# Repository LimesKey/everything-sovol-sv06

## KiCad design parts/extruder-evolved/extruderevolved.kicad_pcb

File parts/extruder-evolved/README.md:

A remake of the Sovol SV06 PCB with extra connectors

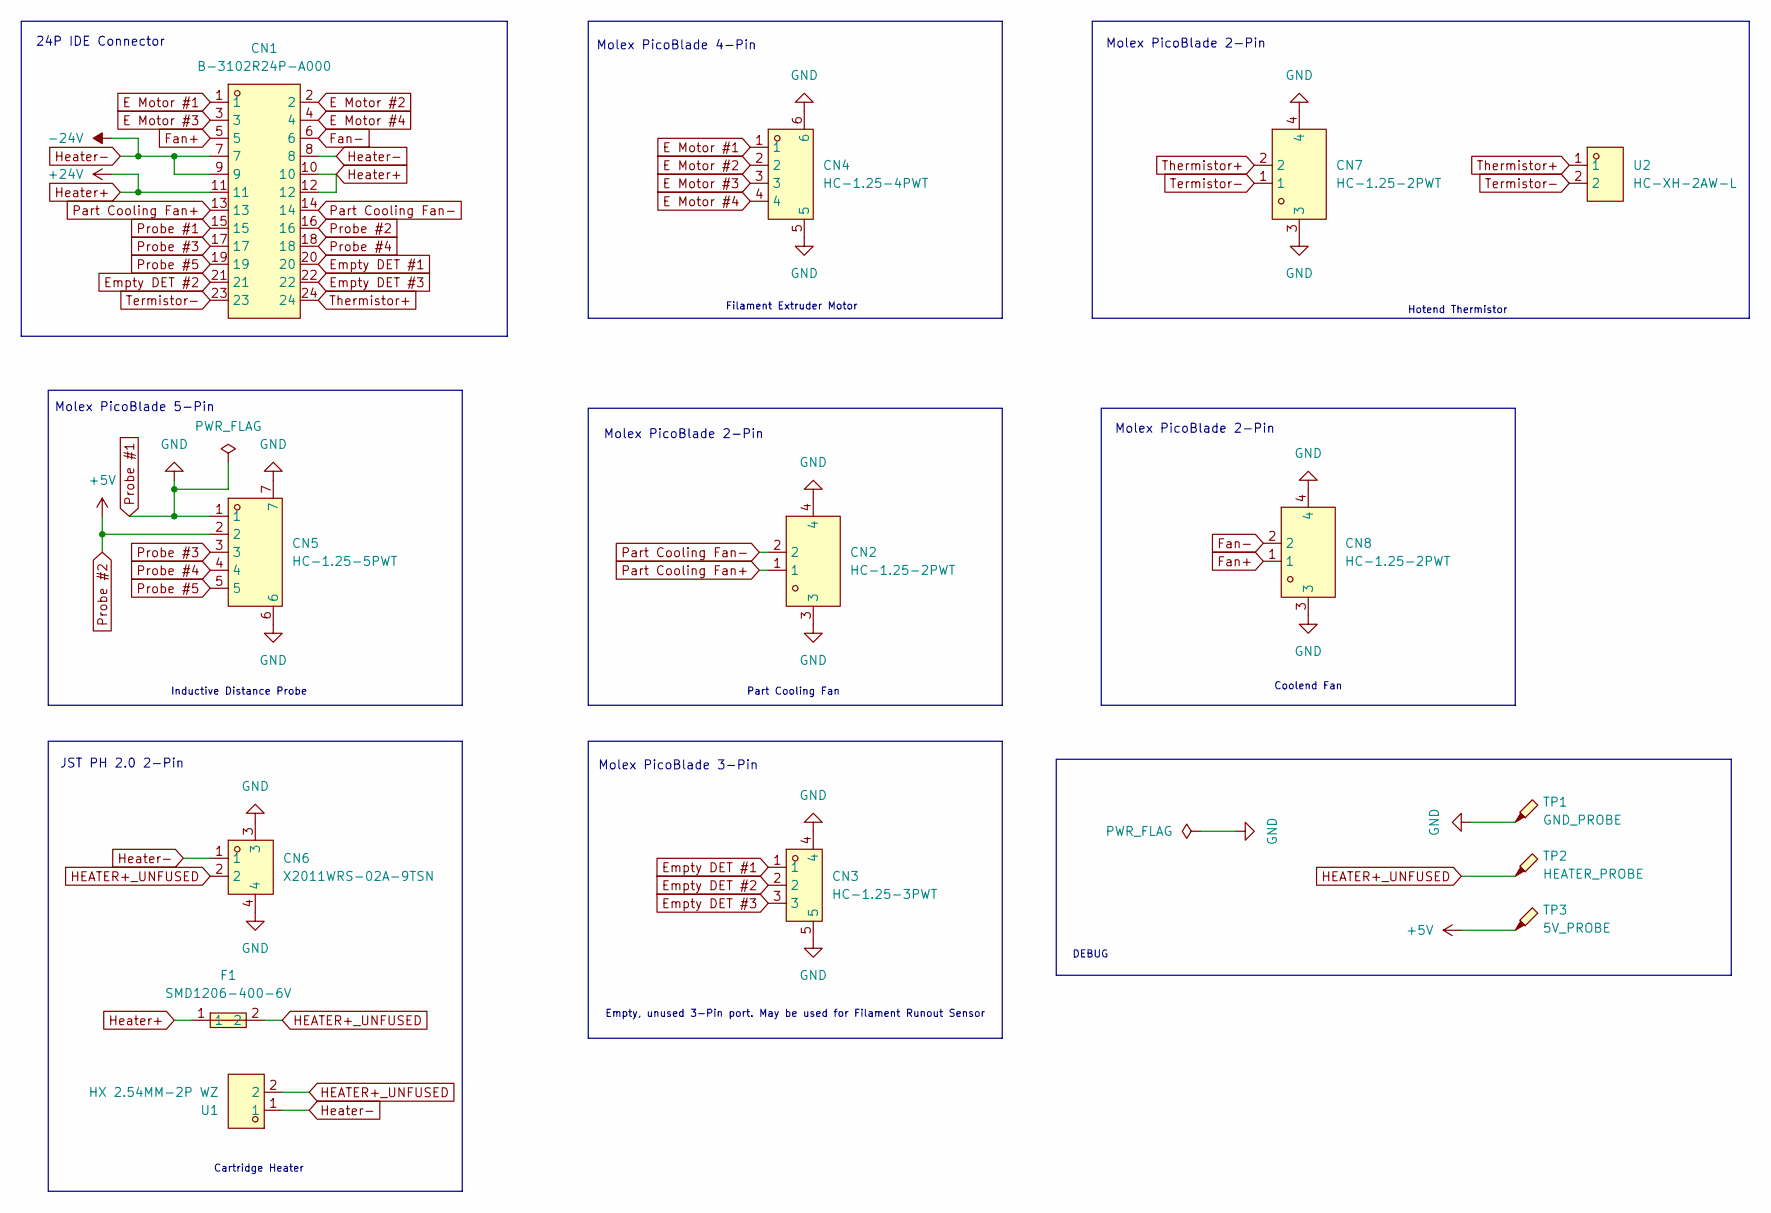
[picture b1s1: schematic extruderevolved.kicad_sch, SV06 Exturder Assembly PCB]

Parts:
CN1: B-3102R24P-A000; IDC-TH_24P-P2.00_B-3102R24P-A000; LCSC Part C383593
CN2, CN7, CN8: HC-1.25-2PWT; CONN-SMD_2P-P1.25-HC-1.25-2PWT; LCSC Part C2845379
CN3: HC-1.25-3PWT; CONN-SMD_HC-1.25-3PWT; LCSC Part C2845380
CN4: HC-1.25-4PWT; CONN-SMD_4P-P1.25-HC-1.25-4PWT; LCSC Part C2845381
CN5: HC-1.25-5PWT; CONN-SMD_5P-P1.25_HCTL_HC-1.25-5PWT; LCSC Part C2845382
CN6: X2011WRS-02A-9TSN; CONN-SMD_2P-P2.00_XKB_X2011WRS-02A-9TSN; LCSC Part C571320
F1: SMD1206-400-6V; F1206; LCSC Part C2760306
TP1: GND_PROBE; TestPoint_THTPad_D2.5mm_Drill1.2mm
TP2: HEATER_PROBE; TestPoint_THTPad_D2.5mm_Drill1.2mm
TP3: 5V_PROBE; TestPoint_THTPad_D2.5mm_Drill1.2mm
U1: HX 2.54MM-2P WZ; CONN-TH_2P-P2.50_HX-2.54MM-2P-WZ; LCSC Part C7543444
U2: HC-XH-2AW-L; CONN-TH_2P-P2.50_HC-XH-2AW-G; LCSC Part C7466689

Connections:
E Motor #1: CN1.1, CN4.1
E Motor #2: CN1.2, CN4.2
E Motor #3: CN1.3, CN4.3
E Motor #4: CN1.4, CN4.4
Empty DET #1: CN1.20, CN3.1
Empty DET #2: CN1.21, CN3.2
Empty DET #3: CN1.22, CN3.3
Fan+: CN1.5, CN8.1
Fan-: CN1.6, CN8.2
HEATER+_UNFUSED: CN6.2, F1.2, TP2.1, U1.2
Heater+: CN1.10, CN1.11, CN1.12, F1.1
Heater-: CN1.7, CN1.8, CN1.9, CN6.1, U1.1
Part Cooling Fan+: CN1.13, CN2.1
Part Cooling Fan-: CN1.14, CN2.2
Probe #1: CN1.15, CN2.3, CN2.4, CN3.4, CN3.5, CN4.5, CN4.6, CN5.1, CN5.6, CN5.7, CN6.3, CN6.4, CN7.3, CN7.4, CN8.3, CN8.4, TP1.1
Probe #2: CN1.16, CN5.2, TP3.1
Probe #3: CN1.17, CN5.3
Probe #4: CN1.18, CN5.4
Probe #5: CN1.19, CN5.5
Termistor-: CN1.23, CN7.1, U2.2
Thermistor+: CN1.24, CN7.2, U2.1

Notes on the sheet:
24P IDE Connector
Molex PicoBlade 5-Pin
Molex PicoBlade 4-Pin
Molex PicoBlade 2-Pin
JST PH 2.0 2-Pin
Inductive Distance Probe
DEBUG
Empty, unused 3-Pin port. May be used for Filament Runout Sensor
Part Cooling Fan
Filament Extruder Motor
Coolend Fan
Molex PicoBlade 3-Pin
Cartridge Heater
Hotend Thermistor

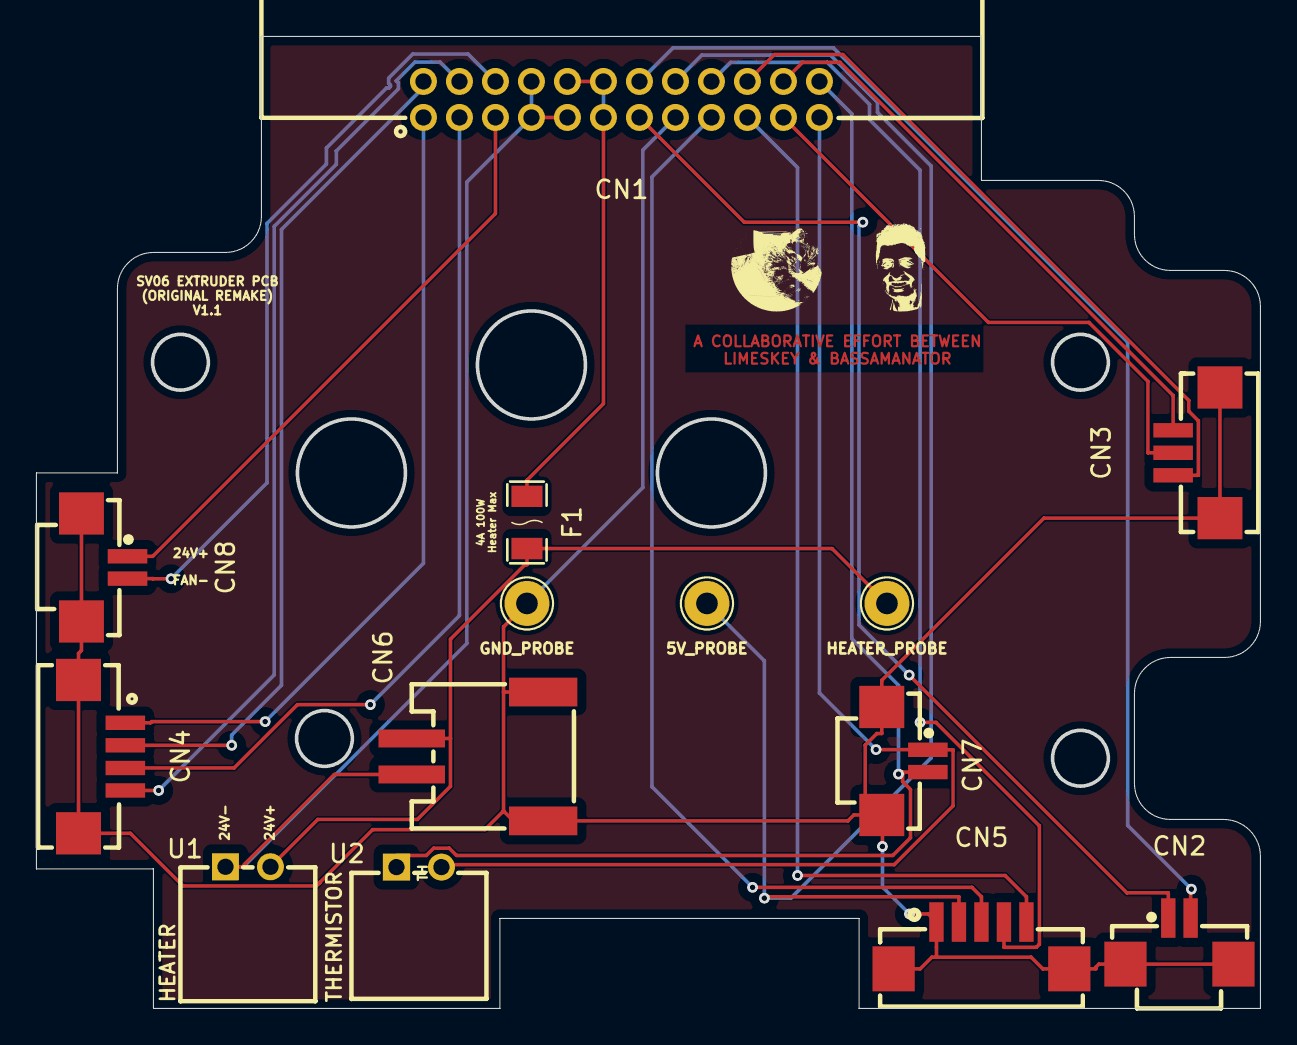
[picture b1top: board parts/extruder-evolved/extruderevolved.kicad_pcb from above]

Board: 2 copper layers, 67.9 x 53.9 mm, 15 parts (0 on the bottom side), 21 nets.

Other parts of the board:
basamator: LOGO; basa

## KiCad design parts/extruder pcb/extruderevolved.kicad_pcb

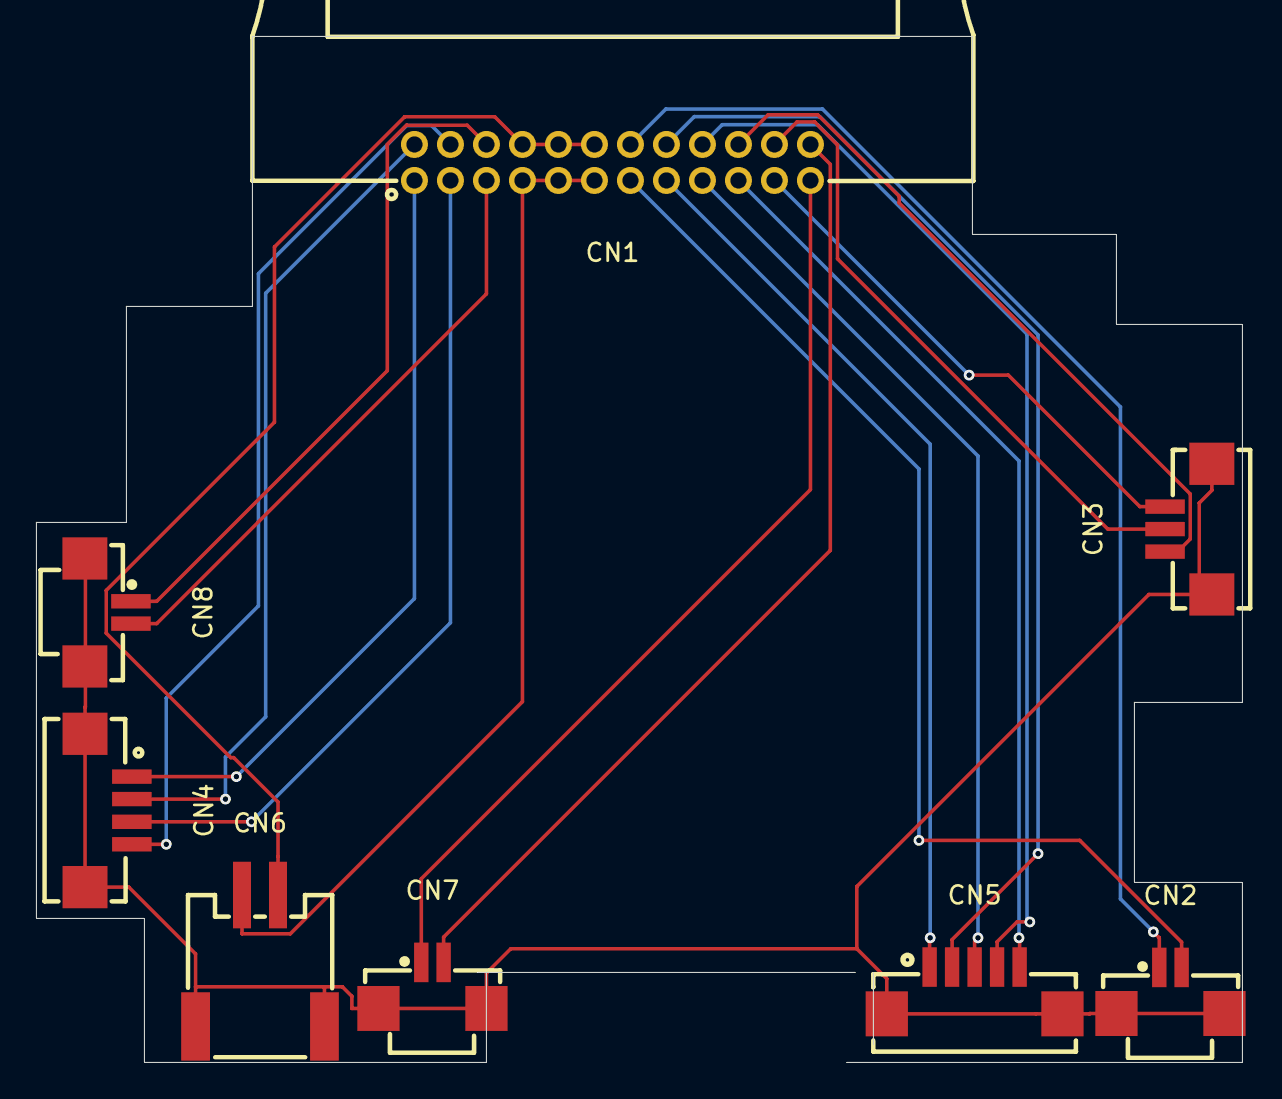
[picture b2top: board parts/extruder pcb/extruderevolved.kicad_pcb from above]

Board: 2 copper layers, 67.0 x 57.0 mm, 8 parts (0 on the bottom side), 21 nets.

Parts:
CN1: B-3102R24P-A000; IDC-TH_24P-P2.00_B-3102R24P-A000
CN2, CN7, CN8: HC-1.25-2PWT; CONN-SMD_2P-P1.25-HC-1.25-2PWT
CN3: HC-1.25-3PWT; CONN-SMD_HC-1.25-3PWT
CN4: HC-1.25-4PWT; CONN-SMD_4P-P1.25-HC-1.25-4PWT
CN5: HC-1.25-5PWT; CONN-SMD_5P-P1.25_HCTL_HC-1.25-5PWT
CN6: X2011WRS-02A-9TSN; CONN-SMD_2P-P2.00_XKB_X2011WRS-02A-9TSN

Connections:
E Motor #1: CN1.1, CN4.1
E Motor #2: CN1.2, CN4.2
E Motor #3: CN1.3, CN4.3
E Motor #4: CN1.4, CN4.4
Empty "DET" #1: CN1.20, CN3.1
Empty "DET" #2: CN1.22, CN3.2
Empty "DET" #3: CN1.21, CN3.3
Fan+: CN1.6, CN8.1
Fan-: CN1.5, CN8.2
GND: CN2.3, CN2.4, CN3.4, CN3.5, CN4.5, CN4.6, CN5.6, CN5.7, CN6.3, CN6.4, CN7.3, CN7.4, CN8.3, CN8.4
Heater+: CN1.7, CN1.9, CN1.11, CN6.1
Heater-: CN1.8, CN1.10, CN1.12, CN6.2
Part Cooling Fan+: CN1.14, CN2.1
Part Cooling Fan-: CN1.13, CN2.2
Probe #1: CN1.15, CN5.1
Probe #2: CN1.16, CN5.2
Probe #3: CN1.17, CN5.3
Probe #4: CN1.18, CN5.4
Probe #5: CN1.19, CN5.5
Termistor-: CN1.24, CN7.2
Thermistor+: CN1.23, CN7.1

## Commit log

2024-08-17 add files
